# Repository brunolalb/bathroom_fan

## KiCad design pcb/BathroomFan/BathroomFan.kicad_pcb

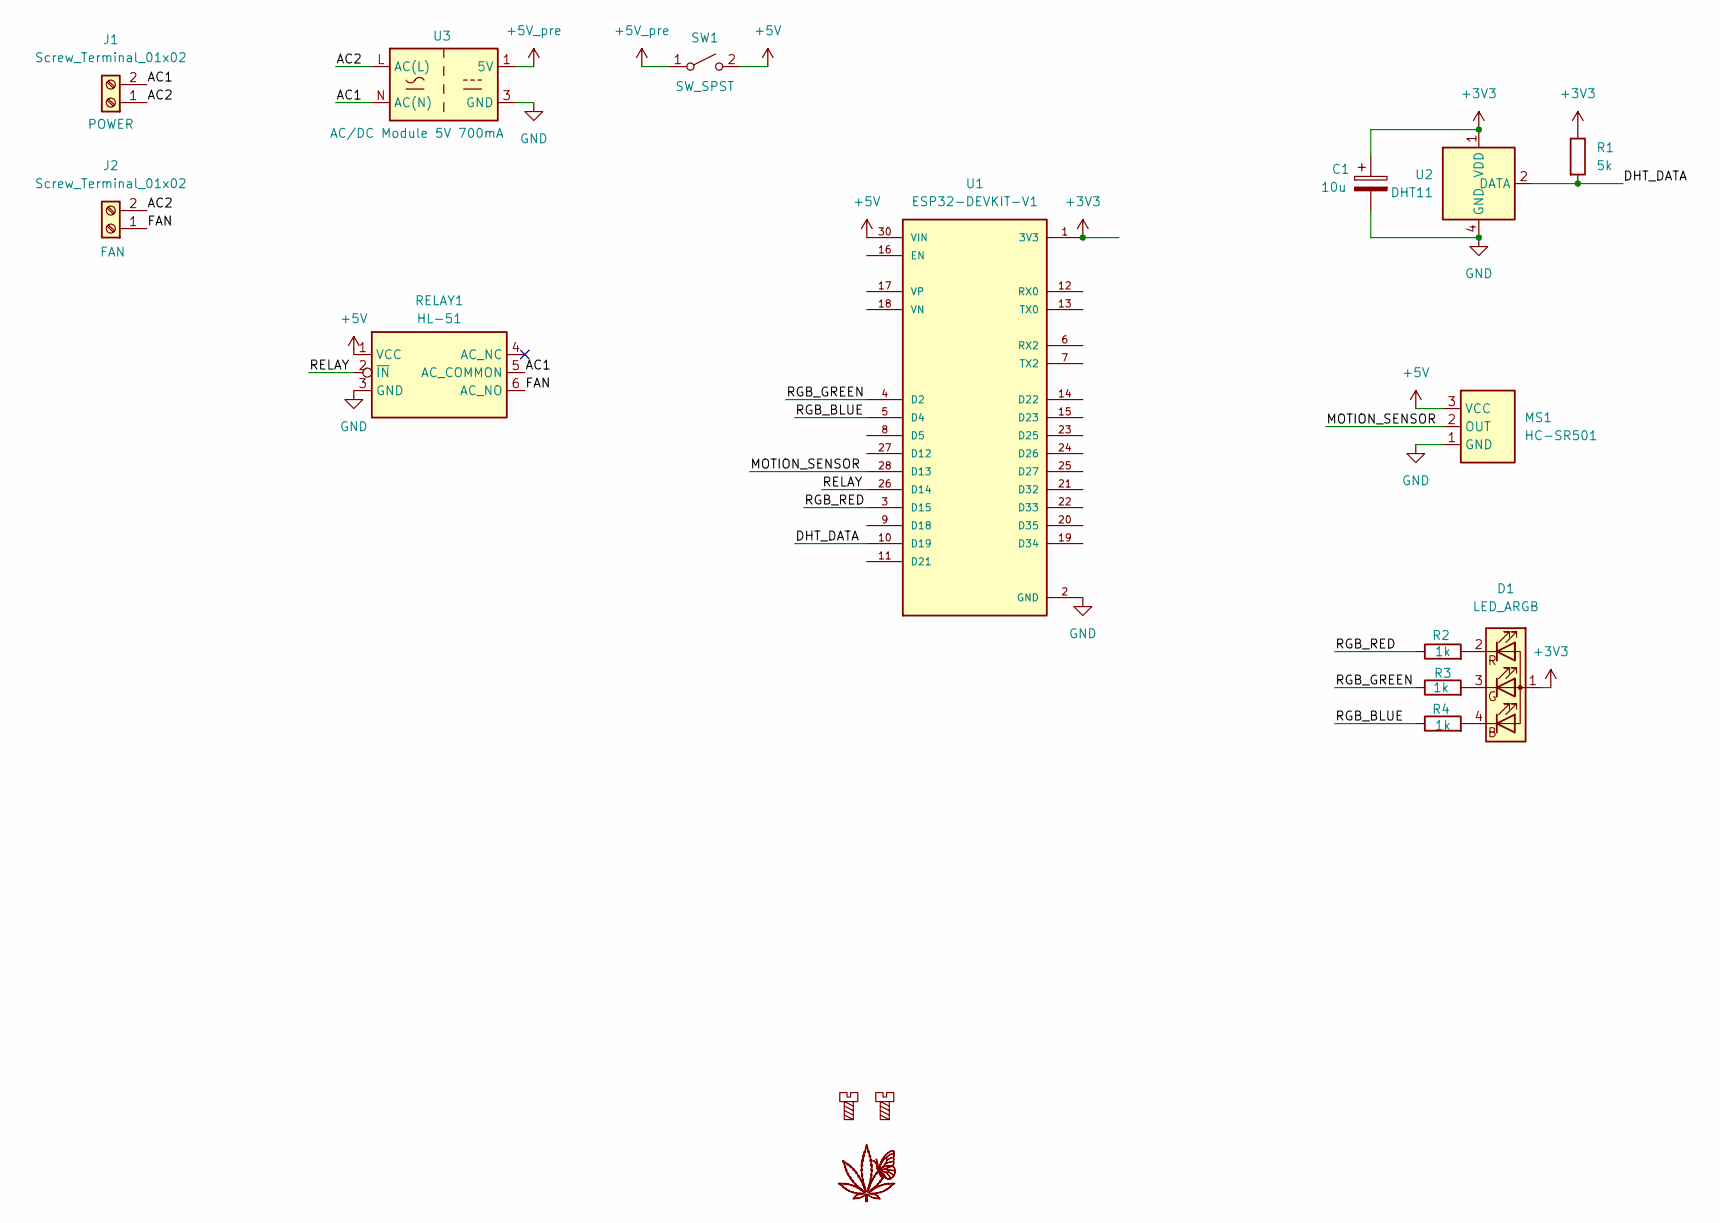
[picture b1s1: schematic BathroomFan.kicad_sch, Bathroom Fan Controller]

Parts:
C1: 10u; CP_Radial_D4.0mm_P2.00mm
D1: LED_ARGB; PinHeader_1x04_P2.54mm_Vertical
G1: LOGO
H1, H2: MountingScrew; MountingHole_4.3mm_M4
J1, J2: Screw_Terminal_01x02; TerminalBlock_Phoenix_MKDS-1,5-2-5.08_1x02_P5.08mm_Horizont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
MS1: HC-SR501; PinHeader_1x03_P2.54mm_Vertical
R1: 5k; R_0805_2012Metric_Pad1.20x1.40mm_HandSolder
R2, R3, R4: 1k; R_0805_2012Metric_Pad1.20x1.40mm_HandSolder
RELAY1: HL-51
SW1: SW_SPST; PinHeader_1x02_P2.54mm_Vertical
U1: ESP32-DEVKIT-V1; ESP32_DEVKIT_V1
U2: DHT11; PinHeader_1x04_P2.54mm_Vertical
U3: AC/DC Module 5V 700mA; ACDC_Module_5V_700mA

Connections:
+3V3: C1.1, D1.1 (A), R1.1, U1.1 (3V3), U2.1 (VDD)
+5V: MS1.3 (VCC), RELAY1.1 (VCC), SW1.2 (B), U1.30 (VIN)
+5V_pre: SW1.1 (A), U3.1 (5V)
/AC1: J1.2, RELAY1.5 (AC_COMMON), U3.N (AC(N))
/AC2: J1.1, J2.2, U3.L (AC(L))
/DHT_DATA: R1.2, U1.10 (D19), U2.2 (DATA)
/FAN: J2.1, RELAY1.6 (AC_NO)
/MOTION_SENSOR: MS1.2 (OUT), U1.28 (D13)
/RELAY: RELAY1.2 (~IN), U1.26 (D14)
/RGB_BLUE: R4.1, U1.5 (D4)
/RGB_GREEN: R3.1, U1.4 (D2)
/RGB_RED: R2.1, U1.3 (D15)
GND: C1.2, MS1.1 (GND), RELAY1.3 (GND), U1.2 (GND), U1.29 (GND), U2.4 (GND), U3.3 (GND)
unnamed: D1.4 (BK), R4.2
unnamed: D1.3 (GK), R3.2
unnamed: D1.2 (RK), R2.2

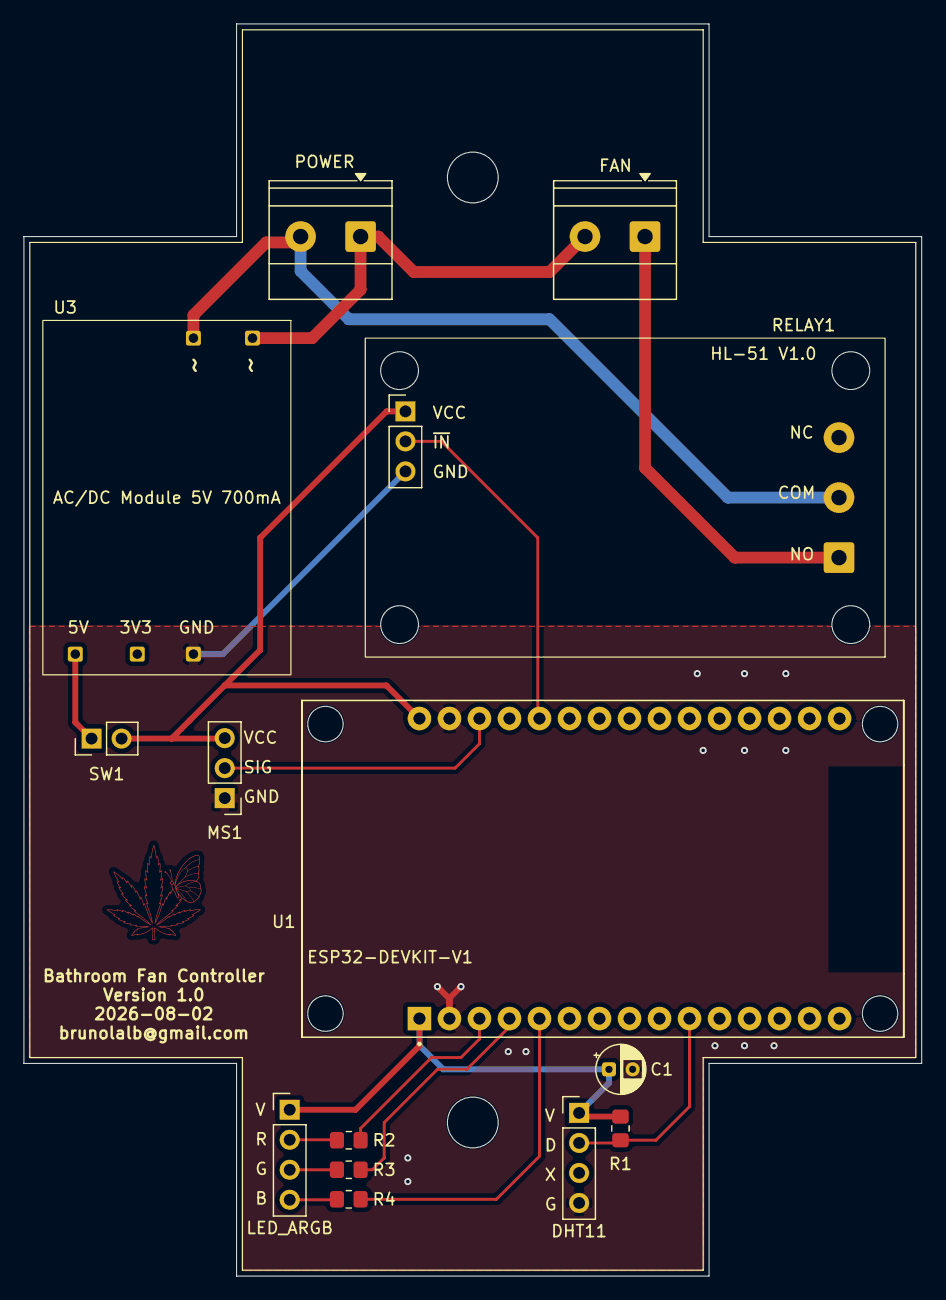
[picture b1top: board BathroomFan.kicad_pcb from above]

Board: 2 copper layers, 76.0 x 106.0 mm, 17 parts (0 on the bottom side), 16 nets.

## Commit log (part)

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2021-09-04 Create bathroom_fan.ino
    has been working for a while...
2021-09-04 Update bathroom_fan.ino
    smol description
2026-02-21 updated libraries
2026-02-21 added ntp client, added a period where the movement detector is ignored
2026-06-29 moved it to platformio
2026-06-29 made it build
2026-06-29 use tzapu's wifimanager instead of doing things manually
2026-06-29 getting ota update to work again
2026-06-29 simplified dht code
2026-06-29 removed mqtt functionality, reviewed wifi setup
2026-06-29 moved led functionality to own lib
2026-06-29 moved humidity and temperature sensor to own library
2026-06-29 moved movement sensor (PIR) to own library
2026-06-29 moved wifi related functionality (wifi, wifimanager, ntp, elegantota) to own lib
2026-06-29 moved hardware config to own header file
2026-06-29 moved switch functionality to own lib
2026-06-29 removed the ota timer, since the elegantota can be initialized only once
2026-06-29 added a config page to the index, you can config humidity limits, quiet times, how long the fan stays on upon motion detection
2026-06-29 reset settings and clear wifi credentials were not working properly. also made the wifimanager portal non blocking and optimized the wifi monitoring task
2026-06-29 control loop was not getting data from the DHT (queue not initialized) and made the movement sensor logic ignore the time if the time is not set
